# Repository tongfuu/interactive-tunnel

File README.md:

# Interactive Tunnel for Children with Postural and Intellectual Disabilities

**More info in the report!**
- abstract
- background
- ideation process
- prototyping
- decomposition/FAST analysis
- methods
- hazard analysis
- regulatory pathway
- evaluation
- discussion
- conclusion

## Demo
video demo: https://www.youtube.com/channel/UC9Hpmn_VhsW2zUZRCOahGSQ

## Summary

Research shows that approximately 38% of children are born with some form of postural disorder. A common technique used to correct these types of disorders in children, comes in the form of an upright tunnel. This type of tunnel is usually referred to as a Barrel Crawl tunnel. Children with postural disorders are placed into this type of tunnel for physical therapy and encouraged to cruise around the diameter of the tunnel. This technique serves to promote straightening of the legs and spine, and ultimately corrects the overall posture of the child.

Spine x-ray of infant with caudal regression

A Durham public school staff member approached our research group for assistance. They claimed that the current tunnel device did not succeed in keeping the children’s attention, for the duration of their therapy. The children also frequently chose to sit down inside the tunnel, which defeated the purpose. The children in this classroom also exhibited a wide variety of intellectual disabilities. Our group was asked to make the device more captivating for the clients, so that they would be engaged for the duration of the therapy session. After much ideation and prototyping, an external device was placed on top of the current tunnel to help solve this issue. We included a motion sensor and LED lights, that would determine if the client is sitting inside the tunnel. The LED lights flashed when touched and animal sounds were activated to stimulate the clients attention. The device allows for either a simple Simon Say’s game or a free play option.

## Design

Pictures of the initial designs

Prototype

Tunnel external device final solution

Optimized PCB 

Real-world testing

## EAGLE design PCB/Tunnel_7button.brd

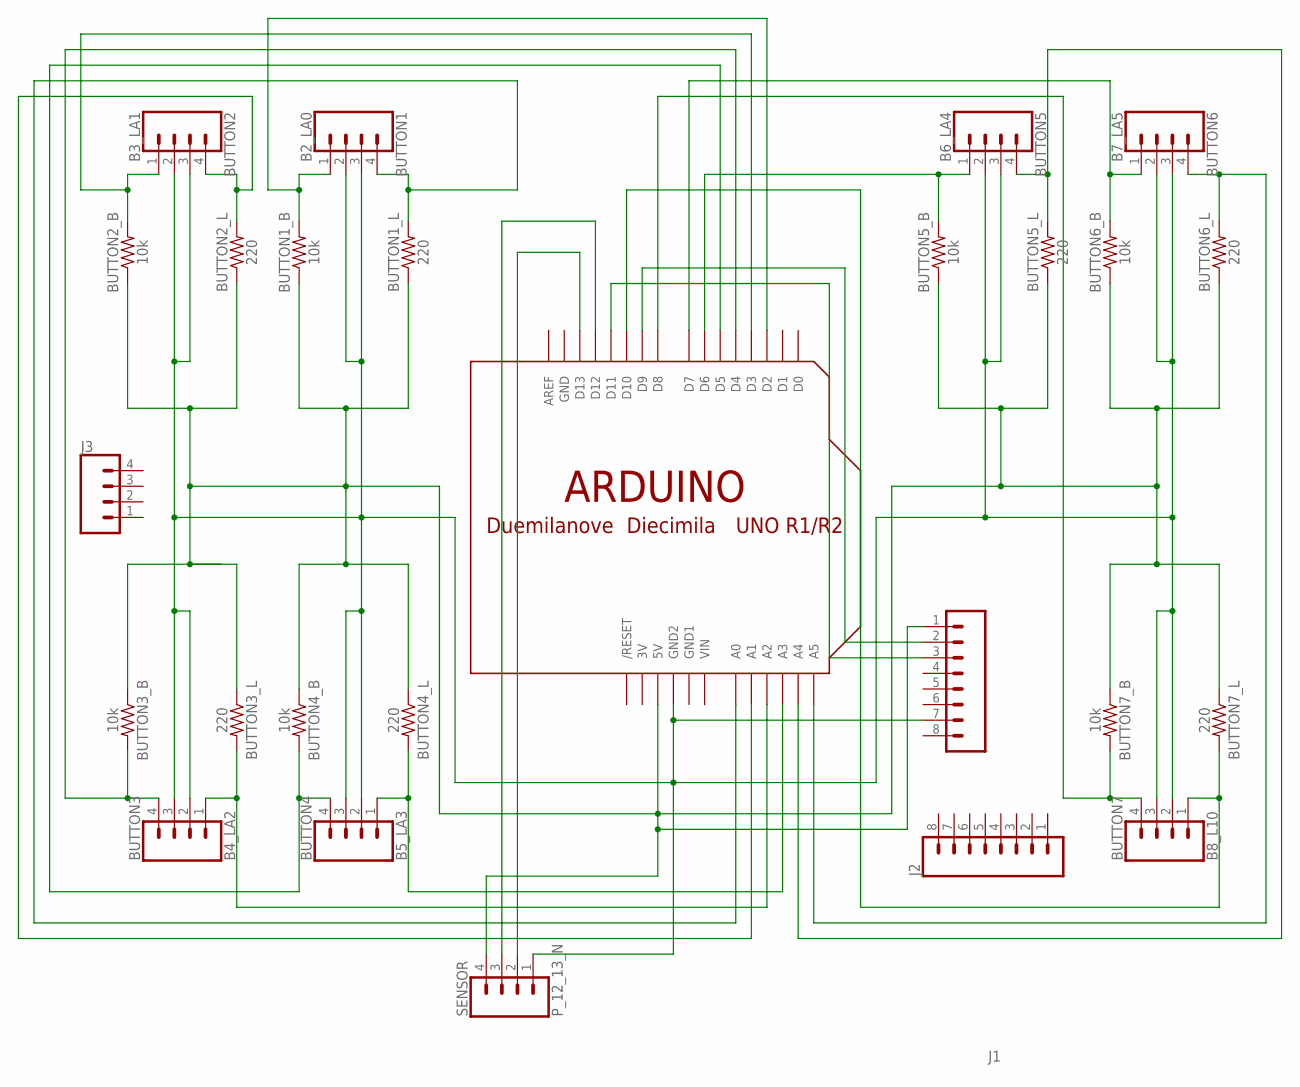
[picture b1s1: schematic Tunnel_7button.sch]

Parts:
BUTTON1: B2_LA0; 1X04_LOCK
BUTTON1_B, BUTTON2_B, BUTTON3_B, BUTTON4_B, BUTTON5_B, BUTTON6_B, BUTTON7_B: 10k; AXIAL-0.3
BUTTON1_L, BUTTON2_L, BUTTON3_L, BUTTON4_L, BUTTON5_L, BUTTON6_L, BUTTON7_L: 220; AXIAL-0.3
BUTTON2: B3_LA1; 1X04_LOCK
BUTTON3: B4_LA2; 1X04_LOCK
BUTTON4: B5_LA3; 1X04_LOCK
BUTTON5: B6_LA4; 1X04_LOCK
BUTTON6: B7_LA5; 1X04_LOCK
BUTTON7: B8_L10; 1X04_LOCK
J1, J2: CONN_08LOCK; 1X08_LOCK
J3: CONN_04LOCK; 1X04_LOCK
SENSOR: P_12_13_N; 1X04_LOCK
U$1: ARDUINO-BPLACE

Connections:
3V: U$1.3V
GND: U$1.GND
GND1: U$1.GND1
unnamed: SENSOR.3, U$1.D12
unnamed: SENSOR.2, U$1.D13
unnamed: BUTTON2.1, BUTTON2_B.P$2 (2), U$1.D3
unnamed: BUTTON2.4, BUTTON2_L.P$2 (2), U$1.A1
unnamed: BUTTON1.1, BUTTON1_B.P$2 (2), U$1.D2
unnamed: BUTTON1.4, BUTTON1_L.P$2 (2), U$1.A0
unnamed: BUTTON1_B.P$1 (1), BUTTON1_L.P$1 (1), BUTTON2_B.P$1 (1), BUTTON2_L.P$1 (1), BUTTON3_B.P$1 (1), BUTTON3_L.P$1 (1), BUTTON4_B.P$1 (1), BUTTON4_L.P$1 (1), BUTTON5_B.P$1 (1), BUTTON5_L.P$1 (1), BUTTON6_B.P$1 (1), BUTTON6_L.P$1 (1), BUTTON7_B.P$1 (1), BUTTON7_L.P$1 (1), J1.1, SENSOR.4, U$1.5V
unnamed: BUTTON5.1, BUTTON5_B.P$2 (2), U$1.D6
unnamed: BUTTON4.1, BUTTON4_L.P$2 (2), U$1.A3
unnamed: BUTTON4.4, BUTTON4_B.P$2 (2), U$1.D5
unnamed: BUTTON5.4, BUTTON5_L.P$2 (2), U$1.A4
unnamed: BUTTON1.2, BUTTON1.3, BUTTON2.2, BUTTON2.3, BUTTON3.2, BUTTON3.3, BUTTON4.2, BUTTON4.3, BUTTON5.2, BUTTON5.3, BUTTON6.2, BUTTON6.3, BUTTON7.2, BUTTON7.3, J1.7, SENSOR.1, U$1.GND2
unnamed: BUTTON3.1, BUTTON3_L.P$2 (2), U$1.A2
unnamed: BUTTON3.4, BUTTON3_B.P$2 (2), U$1.D4
unnamed: BUTTON6.1, BUTTON6_B.P$2 (2), U$1.D7
unnamed: BUTTON6.4, BUTTON6_L.P$2 (2), U$1.A5
unnamed: BUTTON7.1, BUTTON7_L.P$2 (2), U$1.D10
unnamed: BUTTON7.4, BUTTON7_B.P$2 (2), U$1.D8
unnamed: J1.3, U$1.D11
unnamed: J1.2, U$1.D9
VIN: U$1.VIN

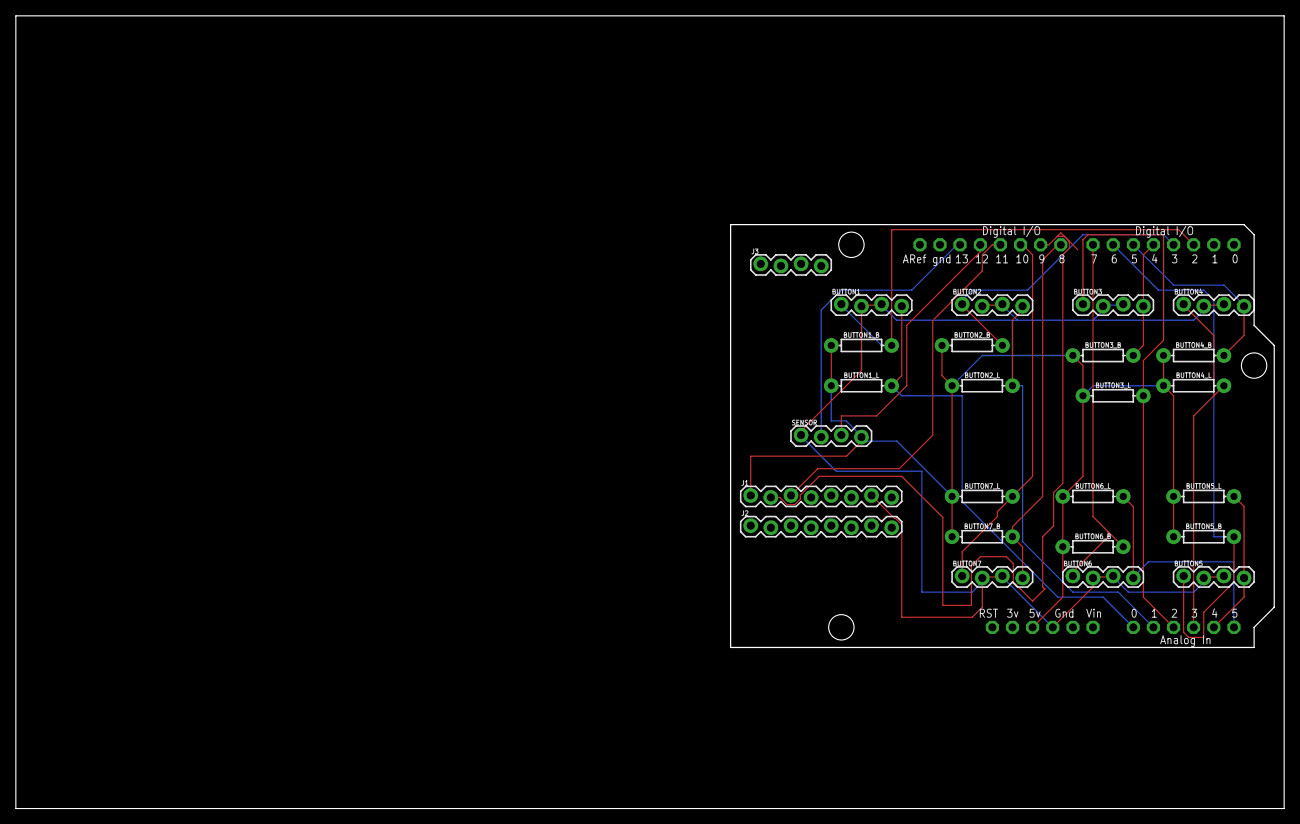
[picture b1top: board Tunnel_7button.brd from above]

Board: 2 copper layers, 160.0 x 100.0 mm, 26 parts (0 on the bottom side), 20 nets.

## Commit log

2021-01-03 uploaded the code
2021-01-03 uploaded the final report
2021-01-03 uploaded the presentation
2021-01-03 uploaded the pcb design
2021-01-03 uploaded the animal sound mp3 files

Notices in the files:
parts and their libraries:
SparkFun-Connectors: Licensing: Creative Commons ShareAlike 4.0 International - https://creativecommons.org/licenses/by-sa/4.0
